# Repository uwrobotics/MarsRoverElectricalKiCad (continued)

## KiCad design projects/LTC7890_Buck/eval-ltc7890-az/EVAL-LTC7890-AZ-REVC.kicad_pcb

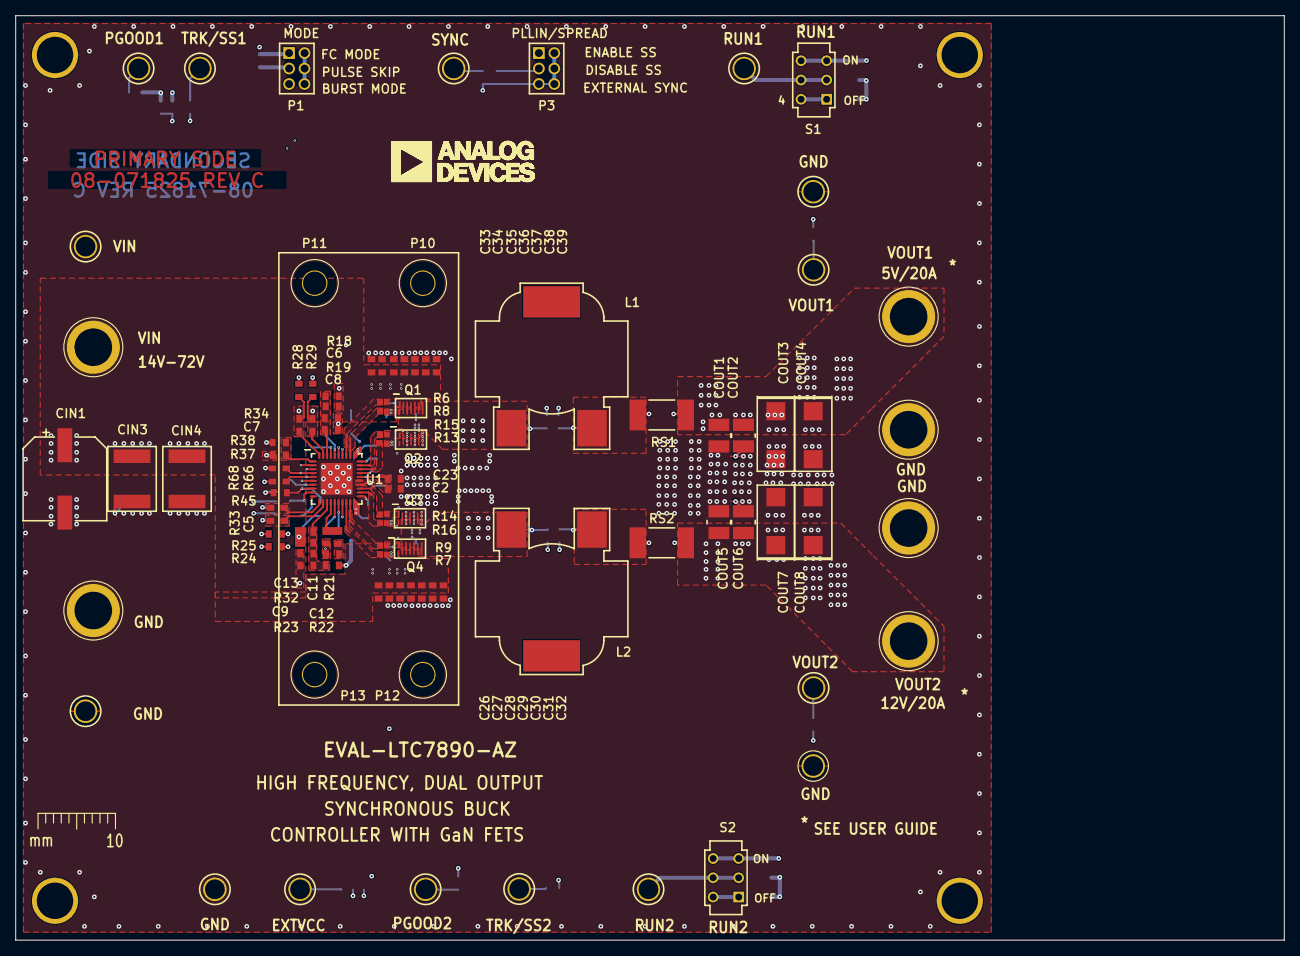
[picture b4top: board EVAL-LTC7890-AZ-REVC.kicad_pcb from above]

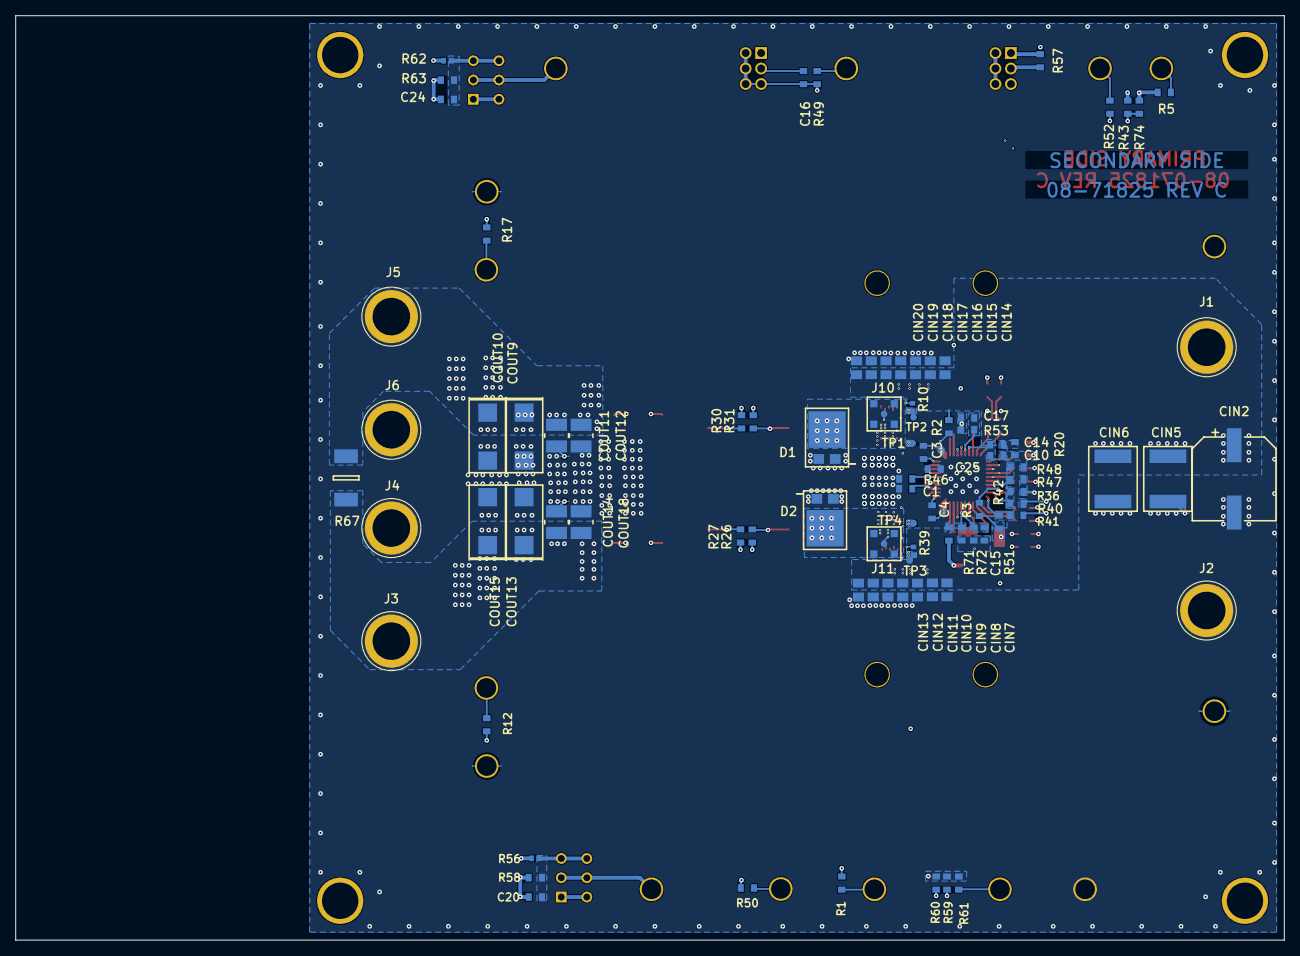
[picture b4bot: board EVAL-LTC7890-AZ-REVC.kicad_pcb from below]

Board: 6 copper layers, 163.8 x 119.4 mm, 180 parts (82 on the bottom side), 62 nets.

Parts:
C1: 4.7uF
C2, C3, C4, C15, C17, C25, C27: 0.1uF
C5, C7: 1000pF
C6, C8, C9, C13, C16: TBD0603
C10, C11, C20, C24: 100pF
C12: 3300pF
C14: 6800pF
C23: 1uF
C26, C28, C29, C30, C31, C32, C33, C34, C35, C36, C37, C38, C39: 0.22uF
CIN1, CIN2: 56UF
CIN3, CIN4, CIN5, CIN6: 22uF
CIN7, CIN8, CIN12, CIN13, CIN14, CIN15, CIN19, CIN20: TBD0805
CIN9, CIN10, CIN11, CIN16, CIN17, CIN18: 1uF
COUT1, COUT2, COUT5, COUT6, COUT11, COUT12, COUT14, COUT18: 22uF
COUT3, COUT4, COUT7, COUT8, COUT9, COUT10, COUT13, COUT15: 150UF
D1, D2: SS10PH10-M3/86A
E1, E2, E3, E4, E5, E6, E7, E8, E9, E10, E11, E12, E13, E16, E17: 2501-2-00-80-00-00-07-0
J1, J2, J3, J4, J5, J6: KFH-032-10ET
J10, J11: 0734152063
L1, L2: 2UH
P1, P3: TMM-103-02-L-D
P10, P11, P12, P13: 9774010243R
Q1, Q2, Q3, Q4: EPC2218
R1, R5, R56, R62: 1MEG
R2, R3, R18, R25, R28, R36, R41, R43, R48, R50, R52, R59: 0
R6: 1.2
R7: 2.2
R8, R9, R13, R14, R15, R16: 1
R10, R39: TBD0402
R12, R17, R24: 10
R19, R22, R26, R27, R30, R31, R33, R34, R38, R40, R42, R45, R46, R47, R51, R53, R58, R60, R61, R63, R66, R68, R71, R72, R74: TBD0603
R20: 3.01K
R21: 5.9K
R23: 1.4MEG
R29: 20
R32, R57: 100K
R37: 75K
R49: 1K
R67: TBD_SPACER_2512
RS1, RS2: 0.0015
S1, S2: JS202011CQN
TP1, TP2, TP3, TP4: TESTPAD
U1: LTC7890RUJM#PBF

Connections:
EXTVCC: C23.2, R46.1, R59.2, R60.2, R61.1, U1.26
GND_POWER: C1.2, C2.2, C23.1, C25.2, C26.2, C27.2, C28.2, C29.2, C30.2, C31.2, C32.2, C33.2, C34.2, C35.2, C36.2, C37.2, C38.2, C39.2, CIN1.N, CIN2.N, CIN3.2, CIN4.2, CIN5.2, CIN6.2, CIN7.2, CIN8.2, CIN9.2, CIN10.2, CIN11.2, CIN12.2, CIN13.2, CIN14.2, CIN15.2, CIN16.2, CIN17.2, CIN18.2, CIN19.2, CIN20.2, COUT1.2, COUT2.2, COUT3.N, COUT4.N, COUT5.2, COUT6.2, COUT7.N, COUT8.N, COUT9.N, COUT10.N, COUT11.2, COUT12.2, COUT13.N, COUT14.2, COUT15.N, COUT18.2, D1.1, D1.2, D2.1, D2.2, E4.1, E7.1, E8.1, E13.1, J2.1, J4.1, J6.1, Q2.2, Q2.4, Q2.6, Q2.8, Q3.2, Q3.4, Q3.6, Q3.8, R46.2, U1.41
GND_SIGNAL: C8.2, C10.1, C11.2, C12.2, C13.2, C15.2, C16.2, C17.2, C20.1, C24.1, P1.5, P3.3, R3.2, R19.2, R20.1, R32.2, R37.1, R40.2, R42.2, R43.2, R48.2, R51.2, R53.2, R58.2, R63.2, R72.1, S1.1, S1.4, S2.1, S2.4, U1.6
INTVCC: C1.1, C2.1, P1.1, P3.1, R1.1, R5.1, R22.2, R36.2, R38.2, R41.2, R45.2, R47.2, R57.1, R71.1, R74.2, U1.24, U1.25
PGOOD1: E2.1, R5.2, R68.1, U1.34
PGOOD2: E1.1, R1.2, R68.2, U1.17
RUN1: E16.1, R66.1, S1.2, S1.5, U1.4
RUN2: E17.1, R66.2, S2.2, S2.5, U1.5
SENSE1+: C7.2, R29.2, R31.2, R34.1, U1.39
SENSE1-: C7.1, R28.2, R30.2, R34.2, U1.40
SENSE2+: C5.1, R24.2, R26.2, R33.1, U1.12
SENSE2-: C5.2, R25.2, R27.2, R33.2, U1.11
UNNAMED_2_ADLTC7890_I172_BGDN1: R15.2, U1.29
UNNAMED_2_ADLTC7890_I172_BGDN2: R16.1, U1.22
UNNAMED_2_ADLTC7890_I172_BGUP1: R13.2, U1.28
UNNAMED_2_ADLTC7890_I172_BGUP2: R14.1, U1.23
UNNAMED_2_ADLTC7890_I172_BOOST1: C3.2, U1.30
UNNAMED_2_ADLTC7890_I172_BOOST2: C4.1, U1.21
UNNAMED_2_ADLTC7890_I172_DRVSET: R3.1, R45.1, U1.8
UNNAMED_2_ADLTC7890_I172_DRVUV: R47.1, R48.1, U1.7
UNNAMED_2_ADLTC7890_I172_DTCA: R36.1, R40.1, U1.9
UNNAMED_2_ADLTC7890_I172_DTCB: R41.1, R42.1, U1.10
UNNAMED_2_ADLTC7890_I172_FREQ: R37.2, R38.1, U1.1
UNNAMED_2_ADLTC7890_I172_ILIM: R71.2, R72.2, U1.16
UNNAMED_2_ADLTC7890_I172_ITH1: C10.2, C14.2, U1.37
UNNAMED_2_ADLTC7890_I172_ITH2: C11.1, R21.1, U1.14
UNNAMED_2_ADLTC7890_I172_MODE: P1.2, P1.4, P1.6, U1.2
UNNAMED_2_ADLTC7890_I172_SW1: C3.1, D1.3, J10.2, J10.3, J10.4, J10.5, L1.1, Q1.2, Q1.4, Q1.6, Q1.8, Q2.3, Q2.5, Q2.7, R31.1, U1.31
UNNAMED_2_ADLTC7890_I172_SW2: C4.2, D2.3, J11.2, J11.3, J11.4, J11.5, L2.2, Q3.3, Q3.5, Q3.7, Q4.2, Q4.4, Q4.6, Q4.8, R26.1, U1.20
UNNAMED_2_ADLTC7890_I172_TGDN1: R8.2, U1.32
UNNAMED_2_ADLTC7890_I172_TGDN2: R9.1, U1.19
UNNAMED_2_ADLTC7890_I172_TGUP1: R6.2, U1.33
UNNAMED_2_ADLTC7890_I172_TGUP2: R7.1, U1.18
UNNAMED_2_ADLTC7890_I172_VIN: C25.1, R2.2, U1.27
UNNAMED_2_ADLTC7890_I172_VPRG1: R43.1, R74.1, U1.35
UNNAMED_2_CAP_I201_N1: C16.1, P3.2, P3.4, P3.5, P3.6, R49.2, U1.3
UNNAMED_2_CAP_I211_N1: C17.1, R52.2, R53.1, U1.36
UNNAMED_2_CAP_I223_N2: C24.2, R62.2, R63.1, S1.3, S1.6
UNNAMED_2_CAP_I271_N2: C20.2, R56.1, R58.1, S2.3, S2.6
UNNAMED_2_CAP_I275_N1: C15.1, R50.1, R51.1, U1.15
UNNAMED_2_CAP_I289_N1: C12.1, R21.2
UNNAMED_2_CAP_I483_N1: C14.1, R20.2
UNNAMED_2_CN6PODDEVEN_I358_N3: P1.3, R57.2
UNNAMED_2_CNBNC5P_I457_CNTR: J10.1, R10.2
UNNAMED_2_CNBNC5P_I458_CNTR: J11.1, R39.2
UNNAMED_2_CNTP1P_I84_N1: E10.1, R49.1
UNNAMED_2_CNTP1P_I85_N1: E11.1, R52.1
UNNAMED_2_CNTP1P_I261_N1: E12.1, R61.2
UNNAMED_2_CNTP1P_I280_N1: E9.1, R50.2
UNNAMED_2_IND_I133_N2: L1.2, R29.1, R30.1, RS1.2
UNNAMED_2_IND_I299_N1: L2.1, R24.1, R27.1, RS2.1
UNNAMED_2_NCTESTPAD_I479_N1: Q1.1, R6.1, R8.1, R10.1, TP2.1
UNNAMED_2_NCTESTPAD_I480_N1: Q2.1, R13.1, R15.1, TP1.1
UNNAMED_2_NCTESTPAD_I481_N1: Q3.1, R14.2, R16.2, TP4.1
UNNAMED_2_NCTESTPAD_I482_N1: Q4.1, R7.2, R9.2, R39.1, TP3.1
VFB1: C6.2, C8.1, R18.2, R19.1, U1.38
VFB2: C9.2, C13.1, R22.1, R23.2, R32.1, U1.13
VIN: C26.1, C27.1, C28.1, C29.1, C30.1, C31.1, C32.1, C33.1, C34.1, C35.1, C36.1, C37.1, C38.1, C39.1, CIN1.P, CIN2.P, CIN3.1, CIN4.1, CIN5.1, CIN6.1, CIN7.1, CIN8.1, CIN9.1, CIN10.1, CIN11.1, CIN12.1, CIN13.1, CIN14.1, CIN15.1, CIN16.1, CIN17.1, CIN18.1, CIN19.1, CIN20.1, E3.1, J1.1, Q1.3, Q1.5, Q1.7, Q4.3, Q4.5, Q4.7, R2.1, R56.2, R62.1
VOSP1: C6.1, E6.1, R17.1, R18.1
VOSP2: C9.1, E5.1, R12.1, R23.1
VOUT1: COUT1.1, COUT2.1, COUT3.P, COUT4.P, COUT9.P, COUT10.P, COUT11.1, COUT12.1, J5.1, R17.2, R28.1, R59.1, R67.1, RS1.1
VOUT2: COUT5.1, COUT6.1, COUT7.P, COUT8.P, COUT13.P, COUT14.1, COUT15.P, COUT18.1, J3.1, R12.2, R25.1, R60.1, R67.2, RS2.2

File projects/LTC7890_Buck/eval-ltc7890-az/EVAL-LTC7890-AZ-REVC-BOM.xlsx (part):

TITLE: Bill of Materials
BOM NO: 05-071825-01-c.csv
DATE: 09/21/2023
DESIGN: 02_071825c_top
TEMPLATE: Z:\allegro\v174_site\cdssetup\template.bom
CALLOUT: C:\Users\kli3\OneDrive - Analog Devices | Inc\Attachments\Current Projects\EVAL-LTC7890-AZ\1-SCH\VER 4\20_071825c\worklib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
ITEM# | Qty | WW_PN | DESCRIPTION | VALUE | JEDEC_TYPE | TOL | VOLTAGE | WATTAGE | LOCATION | MFG | MFG_PN | HLM_STATUS | STOCKROOM_WL | STOCKROOM_GT | STOCKROOM_LK | STOCKROOM_GBO | STOCKROOM_NSH | CUSTOM_PART | DNI
1 | 1 | 08_071825c | PCB | ? | ? | ? | ? | ? | ? | Analog Devices Supplied | 08_071825c | N/A | ? | ? | ? | ? | ? | ? | ?
2 | 1 | E035948 | CAP CER 4.7uF 25V 10% X5R 0603 AEC-Q200 | 4.7uF | C0603 | 10 | 25V | N/A | C1 | MURATA | GRT188R61E475KE13D | REL | N/A | N/A | N/A | N/A | N/A | ? | ?
4 | 1 | E013802 | CAP CER 100pF 50V 10% X8R 0603 | 100pF | C0603 | 10 | 50V | N/A | C11 | TDK | C1608X8R1H101K | REL | N/A | N/A | N/A | N/A | 7002395 | ? | ?
5 | 1 | E019647 | CAP CER 3300pF 50V 10% X7R 0603 | 3300pF | C0603 | 10 | 50V | N/A | C12 | YAGEO | CC0603KRX7R9BB332 | REL | N/A | N/A | N/A | N/A | N/A | ? | ?
7 | 1 | E007966 | CAP CER 6800pF 50V 10% X7R 0603 | 6800pF | C0603 | 10 | 50V | N/A | C14 | YAGEO | CC0603KRX7R9BB682 | REL | N/A | N/A | N/A | N/A | N/A | ? | ?
8 | 5 | E013746 | CAP CER 0.1uF 25V 10% X7R 0603 | 0.1uF | C0603 | 10 | 25V | N/A | C2,C3,C4,C15,C17 | KEMET | C0603C104K3RACTU | REL | N/A | 40302JH282 | N/A | 1285_CAB3 | 7002122 | ? | ?
9 | 2 | E024743 | CAP CER 100pF 50V 10% X7R 0603 | 100pF | C0603 | 10 | 50V | N/A | C20,C24 | KEMET | C0603C101K5RAC | REL | N/A | N/A | N/A | N/A | N/A | ? | ?
10 | 1 | E033832 | CAP CER 1uF 25V 10% X7R 0603 AEC-Q200 | 1uF | C0603 | 10 | 25V | N/A | C23 | MURATA | GCM188R71E105KA64D | REL | N/A | N/A | N/A | N/A | N/A | ? | ?
11 | 2 | E024908 | CAP CER 0.1uF 100V 10% X7R 0603 | 0.1uF | C0603 | 10 | 100V | N/A | C25,C27 | MURATA | GRM188R72A104KA35D | REL | N/A | N/A | N/A | N/A | N/A | ? | ?
12 | 13 | E031432 | NRND - CAP CER 0.22uF 100V 10% X7S 0603 AEC-Q200 | 0.22uF | C0603 | 10 | 100V | N/A | C26,C28,C29,C30,C31,C32,C33,C34,C35,C36,C37,C38,C39 | TAIYO YUDEN | HMK107C7224KAHTE | RWC | N/A | N/A | N/A | N/A | N/A | ? | ?
13 | 2 | E042649 | CAP CER 1000pF 25V 10% X7R 0603 | 1000pF | C0603 | 10 | 25V | N/A | C5,C7 | AVX CORPORATION | 06033C102KAT2A | REL | N/A | N/A | N/A | N/A | N/A | ? | ?
14 | 2 | E062303 | CAP ALUM POLY 56UF 80V 20% 0.028OHM 0.98A 1000H 10X12.6MM | 56UF | CPLSMSQ406H500 | 20 | 80V | N/A | CIN1,CIN2 | PANASONIC | 80SXV56M | REL | N/A | N/A | N/A | N/A | N/A | ? | ?
15 | 6 | E014208 | CAP CER 1uF 100V 10% X7S 0805 | 1uF | C0805 | 10 | 100V | N/A | CIN9,CIN10,CIN11,CIN16,CIN17,CIN18 | TDK | C2012X7S2A105K125AB | REL | N/A | N/A | N/A | N/A | 7002691 | ? | ?
16 | 8 | E000383 | DO NOT INSTALL (TBD_C0805) PLEASE USE SYM_3 AND/OR SYM_4 | TBD0805 | C0805 | TBD0805 | TBD0805 | N/A | CIN7,CIN8,CIN12,CIN13,CIN14,CIN15,CIN19,CIN20 | TBD0805 | TBD0805 | REL | TBD0805 | N/A | N/A | N/A | N/A | ? | ?
18 | 8 | E011548 | CAP CER 22uF 16V 10% X7R 1210 | 22uF | C1210-2 | 10 | 16V | N/A | COUT1,COUT2,COUT5,COUT6,COUT11,COUT12,COUT14,COUT18 | MURATA | GRM32ER71C226KEA8L | REL | N/A | N/A | N/A | N/A | 7000787 | ? | ?
19 | 4 | E046068 | CAP TANT POLY 150UF 16V 20% 7343 0.05 OHM | 150UF | C7343-31 | 20 | 16V | N/A | COUT4,COUT8,COUT10,COUT15 | PANASONIC | 16TQC150MYF | REL | N/A | N/A | N/A | N/A | N/A | ? | ?
22 | 15 | E031108 | CONN-PCB SOLDER TERMINAL TEST POINT TURRET 0.094" MTG. HOLE PCB 0.062 INCH THK | 2501-2-00-80-00-00-07-0 | CNMILLMAX2501 | N/A | N/A | N/A | E1,E2,E3,E4,E5,E6,E7,E8,E9,E10,E11,E12,E13,E16,E17 | MILL-MAX | 2501-2-00-80-00-00-07-0 | REL | N/A | N/A | N/A | N/A | N/A | ? | ?
23 | 6 | E039893 | CONN-PCB THREADED BROACHING STUD, 625MIL LENGTH | KFH-032-10ET | CNPEMKFH-032 | N/A | N/A | N/A | J1,J2,J3,J4,J5,J6 | PENN ENGINEERING | KFH-032-10ET | REL | N/A | N/A | N/A | N/A | N/A | ? | ?
25 | 2 | E047808 | IND POWER SHIELDED WIREWOUND 2UH 20% 100KHZ 40A 1.34MOHM 18.7X19.18MM AEC-Q200 | 2UH | LSML755W365H420 | 20 | N/A | N/A | L1,L2 | COILCRAFT INC. | SER2011-202MLD | REL | N/A | N/A | N/A | N/A | N/A | ? | ?
26 | 2 | E043044 | CONN-PCB 6POS UNSHROUDED HEADER VERT 2MM PITCH | TMM-103-02-L-D | CNTHMHDR2X3L236W155H225 | N/A | N/A | N/A | P1,P3 | SAMTEC INC. | TMM-103-02-L-D | REL | N/A | N/A | N/A | N/A | N/A | ? | ?
27 | 4 | E060235 | CONN-PCB 1POS STEEL SPACER WITH M2X0.4 THD | 9774010243R | CNWURTH9774010243R | N/A | N/A | N/A | P10,P11,P12,P13 | WURTH ELEKTRONIK | 9774010243R | REL | N/A | N/A | N/A | N/A | N/A | ? | ?
28 | 4 | E058016 | TRAN MOSFET N-CH GAN 100V 60A | EPC2218 | DIE8_3_5X1_95_A | N/A | N/A | N/A | Q1,Q2,Q3,Q4 | EFFICIENT POWER CONVERSION CORPORATION | EPC2218 | REL | N/A | N/A | N/A | N/A | N/A | ? | ?
29 | 2 | E027219 | RES SMD 1MEG Ohm 5% 1/10W 0603 AEC-Q200 | 1MEG | R0603 | 5 | N/A | 1/10W | R1,R5 | VISHAY | CRCW06031M00JNEA | REL | N/A | N/A | N/A | N/A | 7000369 | ? | ?
31 | 1 | E030868 | RES SMD 10 Ohm 1% 1/10W 0603 AEC-Q200 | 10 | R0603 | 1 | N/A | 1/10W | R12 | VISHAY | CRCW060310R0FKEA | REL | N/A | N/A | N/A | N/A | N/A | ? | ?
32 | 6 | E019639 | RES SMD 1 Ohm 5% 1/16W 0402 AEC-Q200 | 1 | R0402 | 5 | N/A | 1/16W | R8,R9,R13,R14,R15,R16 | VISHAY | CRCW04021R00JNED | REL | N/A | N/A | N/A | N/A | 7005444 | ? | ?
33 | 2 | E003666 | RES SMD 10 Ohm 1% 1/10W 0603 AEC-Q200 | 10 | R0603 | 1 | N/A | 1/10W | R17,R24 | PANASONIC | ERJ-3EKF10R0V | REL | A003-0032-001 | 41816DG315 | FEC 910-995 | N/A | 7005634 | ? | ?
34 | 12 | E007502 | RES SMD 0 Ohm JUMPER 1/10W 0603 AEC-Q200 PRECISION POWER | 0 | R0603 | JUMPER | N/A | 1/10W | R2,R3,R18,R25,R28,R36,R41,R43,R48,R50,R52,R59 | VISHAY | CRCW06030000Z0EA | REL | N/A | N/A | N/A | N/A | 7000371 | ? | ?
36 | 1 | E019212 | RES SMD 3.01K Ohm 0.1% 1/16W 0603 | 3.01K | R0603 | 0.1 | N/A | 1/16W | R20 | TE CONNECTIVITY | CPF0603B3K01E1 | REL | N/A | N/A | N/A | N/A | 7007094 | ? | ?
37 | 1 | E028374 | RES SMD 5.9K Ohm 1% 1/10W 0603 AEC-Q200 | 5.9K | R0603 | 1 | N/A | 1/10W | R21 | PANASONIC | ERJ-3EKF5901V | REL | N/A | N/A | N/A | N/A | N/A | ? | ?
38 | 1 | E024301 | RES SMD 1.4MEG Ohm 1% 1/10W 0603 AEC-Q200 | 1.4MEG | R0603 | 1 | N/A | 1/10W | R23 | VISHAY | CRCW06031M40FKEA | REL | N/A | N/A | N/A | N/A | N/A | ? | ?
39 | 1 | E032358 | RES SMD 20 Ohm 1% 1/10W 0603 AEC-Q200 | 20 | R0603 | 1 | N/A | 1/10W | R29 | VISHAY | CRCW060320R0FKEA | REL | N/A | N/A | N/A | N/A | 7000803 | ? | ?
40 | 1 | E030871 | RES SMD 100K Ohm 1% 1/10W 0603 AEC-Q200 | 100K | R0603 | 1 | N/A | 1/10W | R32 | VISHAY | CRCW0603100KFKEA | REL | N/A | N/A | N/A | N/A | N/A | ? | ?
41 | 1 | E012707 | RES SMD 75K Ohm 1% 1/10W 0603 AEC-Q200 | 75K | R0603 | 1 | N/A | 1/10W | R37 | PANASONIC | ERJ-3EKF7502V | REL | N/A | N/A | N/A | N/A | N/A | ? | ?
42 | 1 | E003678 | RES SMD 1K Ohm 1% 1/10W 0603 AEC-Q200 | 1K | R0603 | 1 | N/A | 1/10W | R49 | PANASONIC | ERJ-3EKF1001V | REL | A003-0032-013 | 41816DG207 | FEC 911-239 | N/A | 7001194 | ? | ?
43 | 2 | E003749 | RES SMD 1MEG Ohm 1% 1/10W 0402 AEC-Q200 | 1MEG | R0402 | 1 | N/A | 1/10W | R56,R62 | PANASONIC | ERJ-2RKF1004X | REL | A003-0035-002 | N/A | N/A | 1686_CAB3 | N/A | ? | ?
44 | 1 | E010279 | RES SMD 100K Ohm 1% 1/10W 0603 AEC-Q200 | 100K | R0603 | 1 | 50V | 1/10W | R57 | PANASONIC | ERJ-3EKF1003V | REL | A003-0032-128 | 41816DG576 | N/A | N/A | N/A | ? | ?
45 | 1 | E041546 | RES SMD 1.2 Ohm 1% 1/16W 0402 AEC-Q200 | 1.2 | R0402 | 1 | N/A | 1/16W | R6 | VISHAY | CRCW04021R20FKED | REL | N/A | N/A | N/A | N/A | N/A | ? | ?
46 | 1 | E004050 | DO NOT INSTALL (TBD_R0603), PLEASE USE SYM_3 AND/OR SYM_4 | TBD0603 | R0603 | TBD0603 | N/A | TBD0603 | R63 | TBD0603 | TBD0603 | REL | TBD0603 | N/A | N/A | N/A | N/A | ? | ?
48 | 1 | E045373 | RES SMD 2.2 OHM 5% 1/16W 0402 AEC-Q200 | 2.2000000000000002 | R0402 | 5 | N/A | 1/16W | R7 | VISHAY | CRCW04022R20JNED | REL | N/A | N/A | N/A | N/A | N/A | ? | ?
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
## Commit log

2026-01-29 push library
2026-01-29 Update Naming Convention
2026-01-29 Initial Commit on Tools
2026-01-29 add documentation
2026-01-29 Update Documentation
2026-01-29 submit pr-template draft
2026-01-29 fix formatting
2026-01-29 Draft for pull request Template (#1)
    submit pr-template draft
2026-01-29 ts will change soon
2026-01-30 new schematic revision
2026-02-02 Placement
2026-02-04 PCB wiring
2026-02-04 Update stuff
2026-02-04 minor fixes
2026-02-05 Minor changes
2026-02-12 Changed a few pad sizes
2026-02-15 update component link
2026-02-18 Change switch orientation, update XT60 name
2026-03-02 New debug branch
2026-03-10 New Schematic
2026-03-13 Schematic update and partial routing
2026-03-16 Fully routed, no via stitching yet
2026-03-18 Added more capacitors
2026-03-19 Add via stitching
2026-03-19 Edit BOM
2026-03-20 Minor BOM fix
2026-03-20 Schematic, placement, simulations
2026-03-26 Finished PCB
2026-03-27 Minor changes 2
2026-03-27 BOM fix
2026-03-28 Added low side fet diode
2026-03-29 Minor changes again
2026-04-19 New Revision
2026-04-20 Minor rewiring
2026-04-20 BOM Recount
2026-04-27 tspmo few vias were not symmetric
